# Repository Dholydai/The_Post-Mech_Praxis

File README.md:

# The_Post-Mech_Praxis
The "post-mechanical typewriter mechanical switch keyboard"... for writers born in the third decade of the 21st century.

_This keyboard is hardwired... plug-n-play. It works with the US-English drivers of Windows and Linux._  

The cases were created using https://github.com/jeffminton/keyboard_stl_generator and OpenSCAD. 
The PCB design and controller program were created by Troy Fletcher: https://github.com/TroyFletcher/vim-colors-synthwave

//Released the Rev 2 keyboard case files. The added screwed fasteners make it very solid. I call it "The Slab."

Please visit https://post-mech.com

1. DO NOT BUILD Rev 2: I am tweaking the two-handed design. I must remake the PCB in total with KiCad to create an editable file. Adding a 92nd switch will make finding a keycap set 50 times easier.

2. GET THE PCB WRAPPED IN A CASE BEFORE FIRING IT UP: Static discharge has damaged several controllers on my bare boards. On very rare occasion #1 exhibits flakey output that is by solved by hot-plugging. Suspect static damage.

3. DO NOT MAKE THIS MISTAKE: I did not trim the leads of switch K8 flush with the PCB. The long lead shorted the switch to ground through the USB-C connector. The brand new Elite-C controller was killed on first power-up.

4. TO REPLACE THE CONTROLLER: Desolder the Elite-C as best you can (you must buy an electric desoldering sucker). Carefully break up the little PCB with needle nose pliers, being careful to avoid twisting the headers. Desolder and remove the torn pieces of through-hole barrels stuck to the header pins. Solder the new controller to the old headers.

Note: Received new Rev 2 PCBs from PCBWay for two-hand keyboards, the quality of the PCBs is excellent... built #4. Also built and tested the reversable PCBs for single-hand Dvorak keyboards designed by Troy Fletcher. Both work!

Dholydai

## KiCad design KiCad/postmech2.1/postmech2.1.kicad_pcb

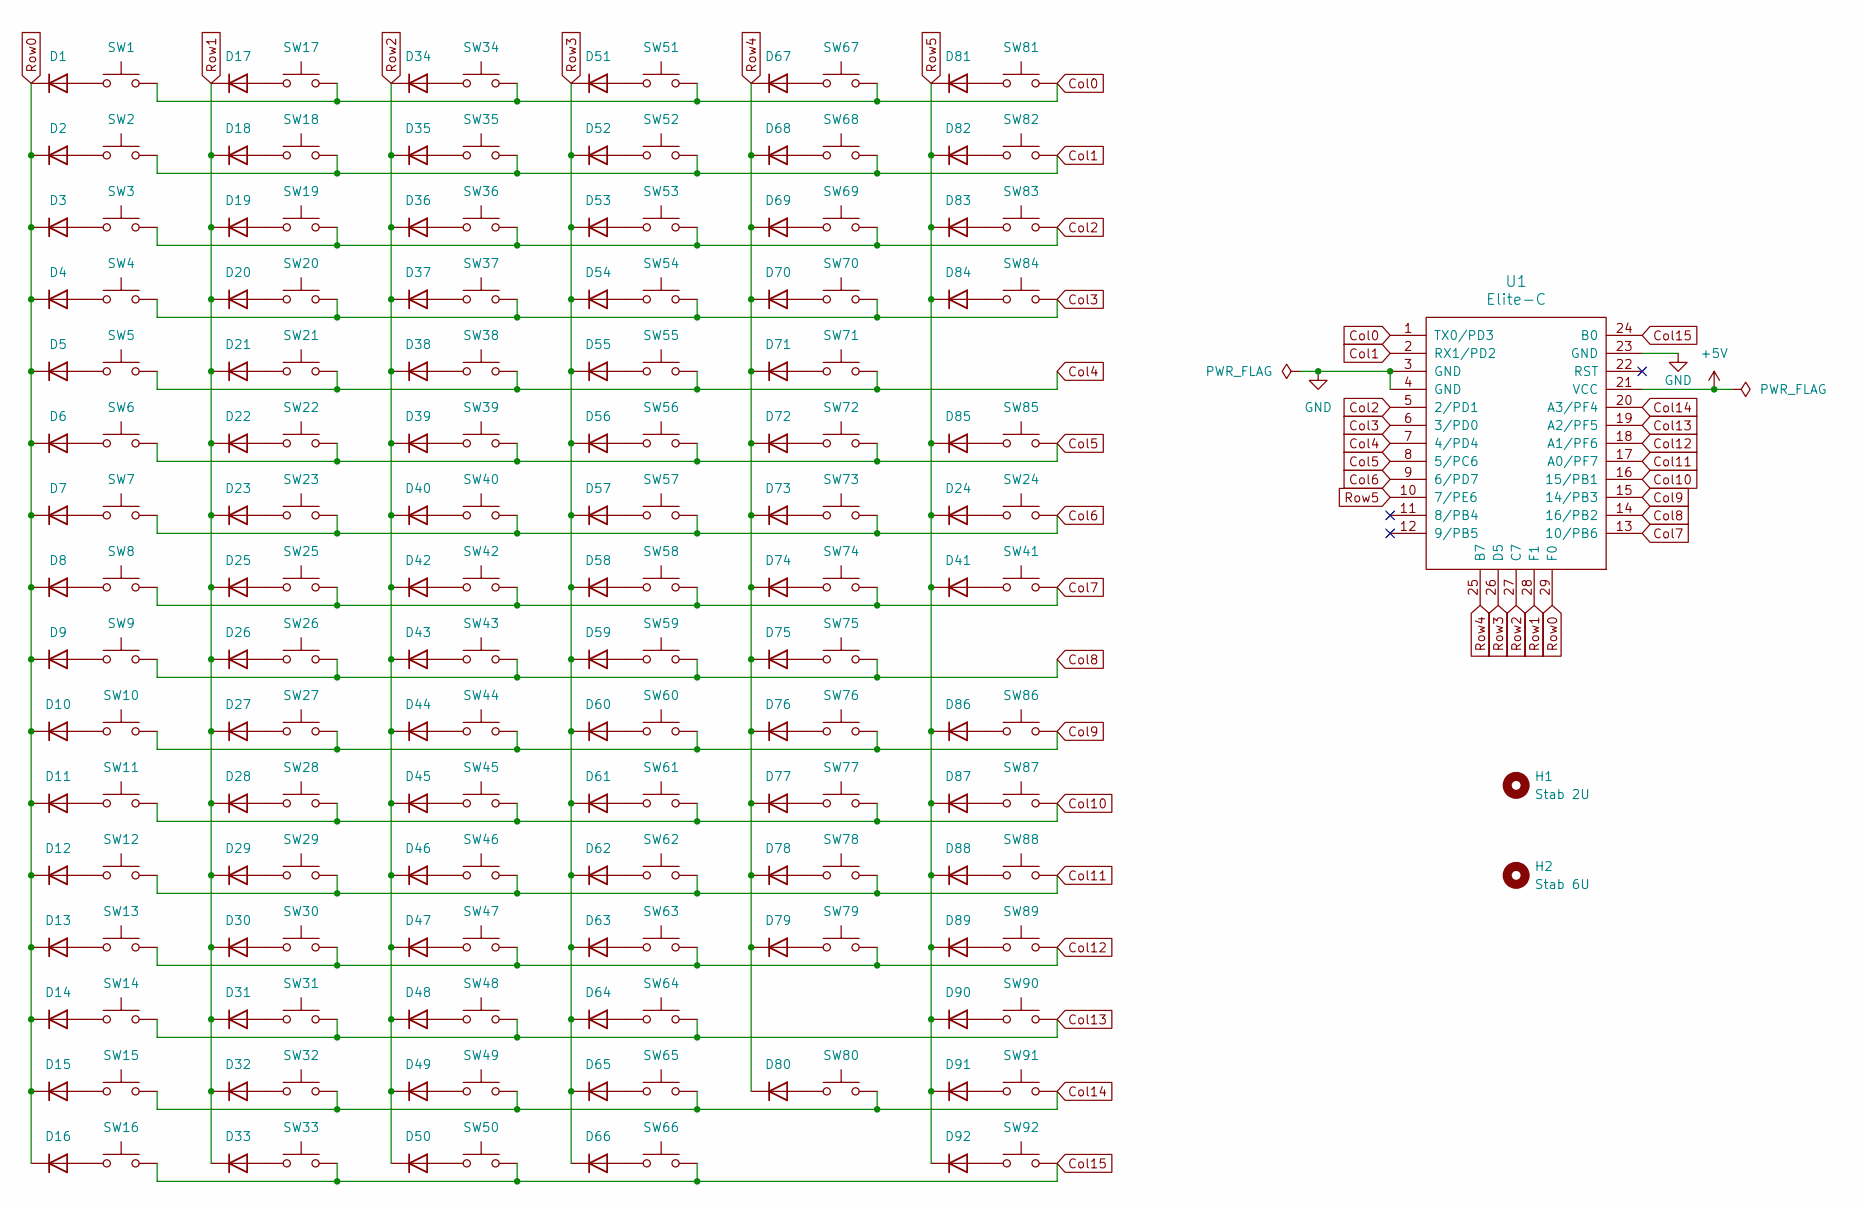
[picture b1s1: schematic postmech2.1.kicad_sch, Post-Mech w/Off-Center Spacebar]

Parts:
D1, D2, D3, D4, D5, D6, D7, D8, D9, D10, D11, D12, D13, D14, D15, D16, D17, D18, D19, D20, D21, D22, D23, D24, D25, D26, D27, D28, D29, D30, D31, D32, D33, D34, D35, D36, D37, D38, D39, D40, D41, D42, D43, D44, D45, D46, D47, D48, D49, D50, D51, D52, D53, D54, D55, D56, D57, D58, D59, D60, D61, D62, D63, D64, D65, D66, D67, D68, D69, D70, D71, D72, D73, D74, D75, D76, D77, D78, D79, D80, D81, D82, D83, D84, D85, D86, D87, D88, D89, D90, D91, D92: 1N4148; Diode_DO-35
H1: Stab 2U; Stabilizer_MX_2.00u
H2: Stab 6U; Stabilizer_MX_6.00u
SW1, SW2, SW3, SW4, SW5, SW6, SW7, SW8, SW9, SW10, SW11, SW12, SW13, SW14, SW15, SW16, SW18, SW19, SW20, SW21, SW22, SW23, SW24, SW25, SW26, SW27, SW28, SW29, SW31, SW32, SW33, SW34, SW35, SW36, SW37, SW38, SW39, SW40, SW41, SW42, SW43, SW44, SW45, SW46, SW47, SW48, SW49, SW50, SW52, SW53, SW54, SW55, SW56, SW58, SW59, SW60, SW61, SW62, SW64, SW65, SW66, SW68, SW69, SW70, SW71, SW72, SW74, SW75, SW76, SW77, SW78, SW80, SW82, SW83, SW87, SW88, SW90, SW91, SW92: SW_Push; MX_PCB_1.00u
SW17, SW30, SW67, SW79: SW_Push; MX_PCB_1.50u
SW51, SW63: SW_Push; MX_PCB_1.75u
SW57, SW81, SW84, SW86, SW89: SW_Push; MX_PCB_1.25u
SW73: SW_Push; MX_PCB_2.00u
SW85: SW_Push; MX_PCB_6.00u_Offset
U1: Elite-C

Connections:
+5V: U1.21 (VCC)
Col0: SW1.2, SW17.2, SW34.2, SW51.2, SW67.2, SW81.2, U1.1 (TX0/PD3)
Col1: SW2.2, SW18.2, SW35.2, SW52.2, SW68.2, SW82.2, U1.2 (RX1/PD2)
Col2: SW3.2, SW19.2, SW36.2, SW53.2, SW69.2, SW83.2, U1.5 (2/PD1)
Col3: SW4.2, SW20.2, SW37.2, SW54.2, SW70.2, SW84.2, U1.6 (3/PD0)
Col4: SW5.2, SW21.2, SW38.2, SW55.2, SW71.2, U1.7 (4/PD4)
Col5: SW6.2, SW22.2, SW39.2, SW56.2, SW72.2, SW85.2, U1.8 (5/PC6)
Col6: SW7.2, SW23.2, SW24.2, SW40.2, SW57.2, SW73.2, U1.9 (6/PD7)
Col7: SW8.2, SW25.2, SW41.2, SW42.2, SW58.2, SW74.2, U1.13 (10/PB6)
Col8: SW9.2, SW26.2, SW43.2, SW59.2, SW75.2, U1.14 (16/PB2)
Col9: SW10.2, SW27.2, SW44.2, SW60.2, SW76.2, SW86.2, U1.15 (14/PB3)
Col10: SW11.2, SW28.2, SW45.2, SW61.2, SW77.2, SW87.2, U1.16 (15/PB1)
Col11: SW12.2, SW29.2, SW46.2, SW62.2, SW78.2, SW88.2, U1.17 (A0/PF7)
Col12: SW13.2, SW30.2, SW47.2, SW63.2, SW79.2, SW89.2, U1.18 (A1/PF6)
Col13: SW14.2, SW31.2, SW48.2, SW64.2, SW90.2, U1.19 (A2/PF5)
Col14: SW15.2, SW32.2, SW49.2, SW65.2, SW80.2, SW91.2, U1.20 (A3/PF4)
Col15: SW16.2, SW33.2, SW50.2, SW66.2, SW92.2, U1.24 (B0)
GND: U1.3 (GND), U1.4 (GND), U1.23 (GND)
unnamed: D1.2 (A), SW1.1
unnamed: D2.2 (A), SW2.1
unnamed: D3.2 (A), SW3.1
unnamed: D4.2 (A), SW4.1
unnamed: D5.2 (A), SW5.1
unnamed: D6.2 (A), SW6.1
unnamed: D7.2 (A), SW7.1
unnamed: D8.2 (A), SW8.1
unnamed: D9.2 (A), SW9.1
unnamed: D10.2 (A), SW10.1
unnamed: D11.2 (A), SW11.1
unnamed: D12.2 (A), SW12.1
unnamed: D13.2 (A), SW13.1
unnamed: D14.2 (A), SW14.1
unnamed: D15.2 (A), SW15.1
unnamed: D16.2 (A), SW16.1
unnamed: D17.2 (A), SW17.1
unnamed: D18.2 (A), SW18.1
unnamed: D19.2 (A), SW19.1
unnamed: D20.2 (A), SW20.1
unnamed: D21.2 (A), SW21.1
unnamed: D22.2 (A), SW22.1
unnamed: D23.2 (A), SW23.1
unnamed: D24.2 (A), SW24.1
unnamed: D25.2 (A), SW25.1
unnamed: D26.2 (A), SW26.1
unnamed: D27.2 (A), SW27.1
unnamed: D28.2 (A), SW28.1
unnamed: D29.2 (A), SW29.1
unnamed: D30.2 (A), SW30.1
unnamed: D31.2 (A), SW31.1
unnamed: D32.2 (A), SW32.1
unnamed: D33.2 (A), SW33.1
unnamed: D34.2 (A), SW34.1
unnamed: D35.2 (A), SW35.1
unnamed: D36.2 (A), SW36.1
unnamed: D37.2 (A), SW37.1
unnamed: D38.2 (A), SW38.1
unnamed: D39.2 (A), SW39.1
unnamed: D40.2 (A), SW40.1
unnamed: D41.2 (A), SW41.1
unnamed: D42.2 (A), SW42.1
unnamed: D43.2 (A), SW43.1
unnamed: D44.2 (A), SW44.1
unnamed: D45.2 (A), SW45.1
unnamed: D46.2 (A), SW46.1
unnamed: D47.2 (A), SW47.1
unnamed: D48.2 (A), SW48.1
unnamed: D49.2 (A), SW49.1
unnamed: D50.2 (A), SW50.1
unnamed: D51.2 (A), SW51.1
unnamed: D52.2 (A), SW52.1
unnamed: D53.2 (A), SW53.1
unnamed: D54.2 (A), SW54.1
unnamed: D55.2 (A), SW55.1
unnamed: D56.2 (A), SW56.1
unnamed: D57.2 (A), SW57.1
unnamed: D58.2 (A), SW58.1
unnamed: D59.2 (A), SW59.1
unnamed: D60.2 (A), SW60.1
unnamed: D61.2 (A), SW61.1
unnamed: D62.2 (A), SW62.1
unnamed: D63.2 (A), SW63.1
unnamed: D64.2 (A), SW64.1
unnamed: D65.2 (A), SW65.1
unnamed: D66.2 (A), SW66.1
unnamed: D67.2 (A), SW67.1
unnamed: D68.2 (A), SW68.1
unnamed: D69.2 (A), SW69.1
unnamed: D70.2 (A), SW70.1
unnamed: D71.2 (A), SW71.1
unnamed: D72.2 (A), SW72.1
unnamed: D73.2 (A), SW73.1
unnamed: D74.2 (A), SW74.1
unnamed: D75.2 (A), SW75.1
unnamed: D76.2 (A), SW76.1
unnamed: D77.2 (A), SW77.1
unnamed: D78.2 (A), SW78.1
unnamed: D79.2 (A), SW79.1
unnamed: D80.2 (A), SW80.1
unnamed: D81.2 (A), SW81.1
unnamed: D82.2 (A), SW82.1
unnamed: D83.2 (A), SW83.1
unnamed: D84.2 (A), SW84.1
unnamed: D85.2 (A), SW85.1
unnamed: D86.2 (A), SW86.1
unnamed: D87.2 (A), SW87.1
unnamed: D88.2 (A), SW88.1
unnamed: D89.2 (A), SW89.1
unnamed: D90.2 (A), SW90.1
unnamed: D91.2 (A), SW91.1
unnamed: D92.2 (A), SW92.1
Row0: D1.1 (K), D2.1 (K), D3.1 (K), D4.1 (K), D5.1 (K), D6.1 (K), D7.1 (K), D8.1 (K), D9.1 (K), D10.1 (K), D11.1 (K), D12.1 (K), D13.1 (K), D14.1 (K), D15.1 (K), D16.1 (K), U1.29 (F0)
Row1: D17.1 (K), D18.1 (K), D19.1 (K), D20.1 (K), D21.1 (K), D22.1 (K), D23.1 (K), D25.1 (K), D26.1 (K), D27.1 (K), D28.1 (K), D29.1 (K), D30.1 (K), D31.1 (K), D32.1 (K), D33.1 (K), U1.28 (F1)
Row2: D34.1 (K), D35.1 (K), D36.1 (K), D37.1 (K), D38.1 (K), D39.1 (K), D40.1 (K), D42.1 (K), D43.1 (K), D44.1 (K), D45.1 (K), D46.1 (K), D47.1 (K), D48.1 (K), D49.1 (K), D50.1 (K), U1.27 (C7)
Row3: D51.1 (K), D52.1 (K), D53.1 (K), D54.1 (K), D55.1 (K), D56.1 (K), D57.1 (K), D58.1 (K), D59.1 (K), D60.1 (K), D61.1 (K), D62.1 (K), D63.1 (K), D64.1 (K), D65.1 (K), D66.1 (K), U1.26 (D5)
Row4: D67.1 (K), D68.1 (K), D69.1 (K), D70.1 (K), D71.1 (K), D72.1 (K), D73.1 (K), D74.1 (K), D75.1 (K), D76.1 (K), D77.1 (K), D78.1 (K), D79.1 (K), D80.1 (K), U1.25 (B7)
Row5: D24.1 (K), D41.1 (K), D81.1 (K), D82.1 (K), D83.1 (K), D84.1 (K), D85.1 (K), D86.1 (K), D87.1 (K), D88.1 (K), D89.1 (K), D90.1 (K), D91.1 (K), D92.1 (K), U1.10 (7/PE6)

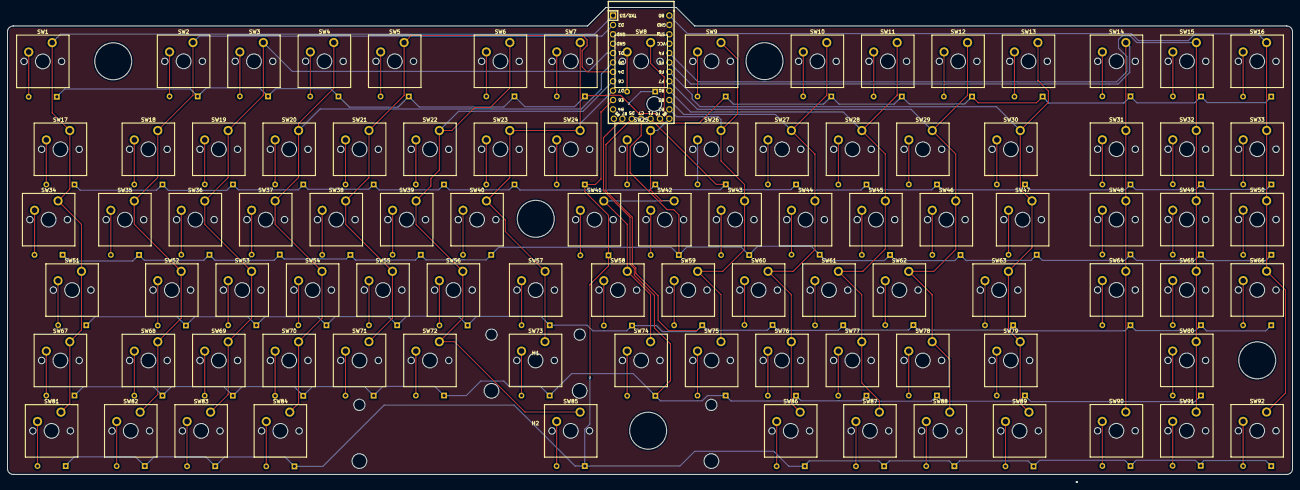
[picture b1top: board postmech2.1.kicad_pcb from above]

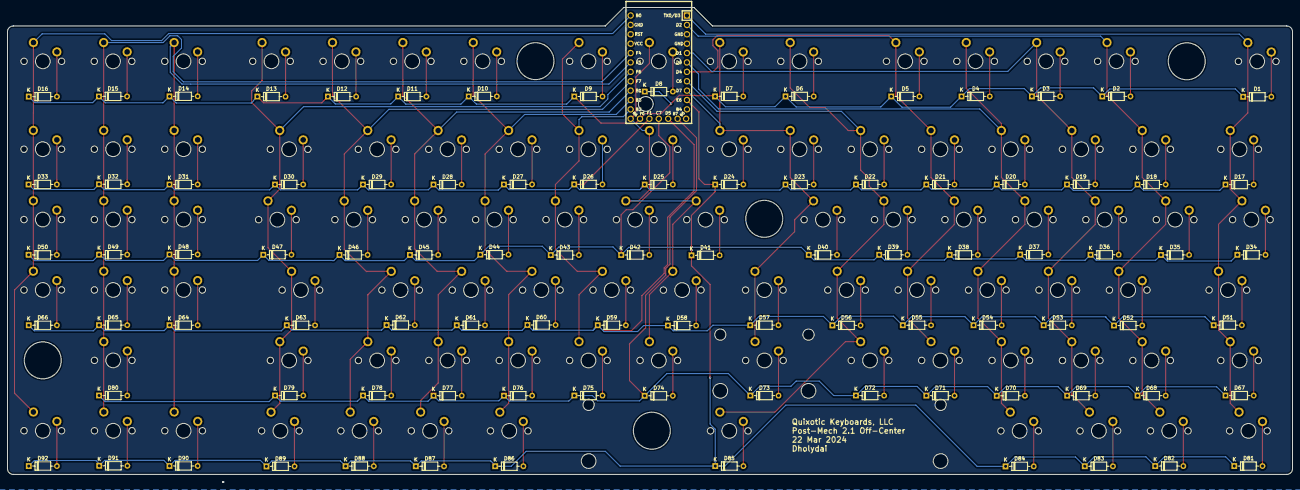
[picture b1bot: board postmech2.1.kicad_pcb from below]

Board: 2 copper layers, 347.8 x 128.5 mm, 187 parts (92 on the bottom side), 115 nets.

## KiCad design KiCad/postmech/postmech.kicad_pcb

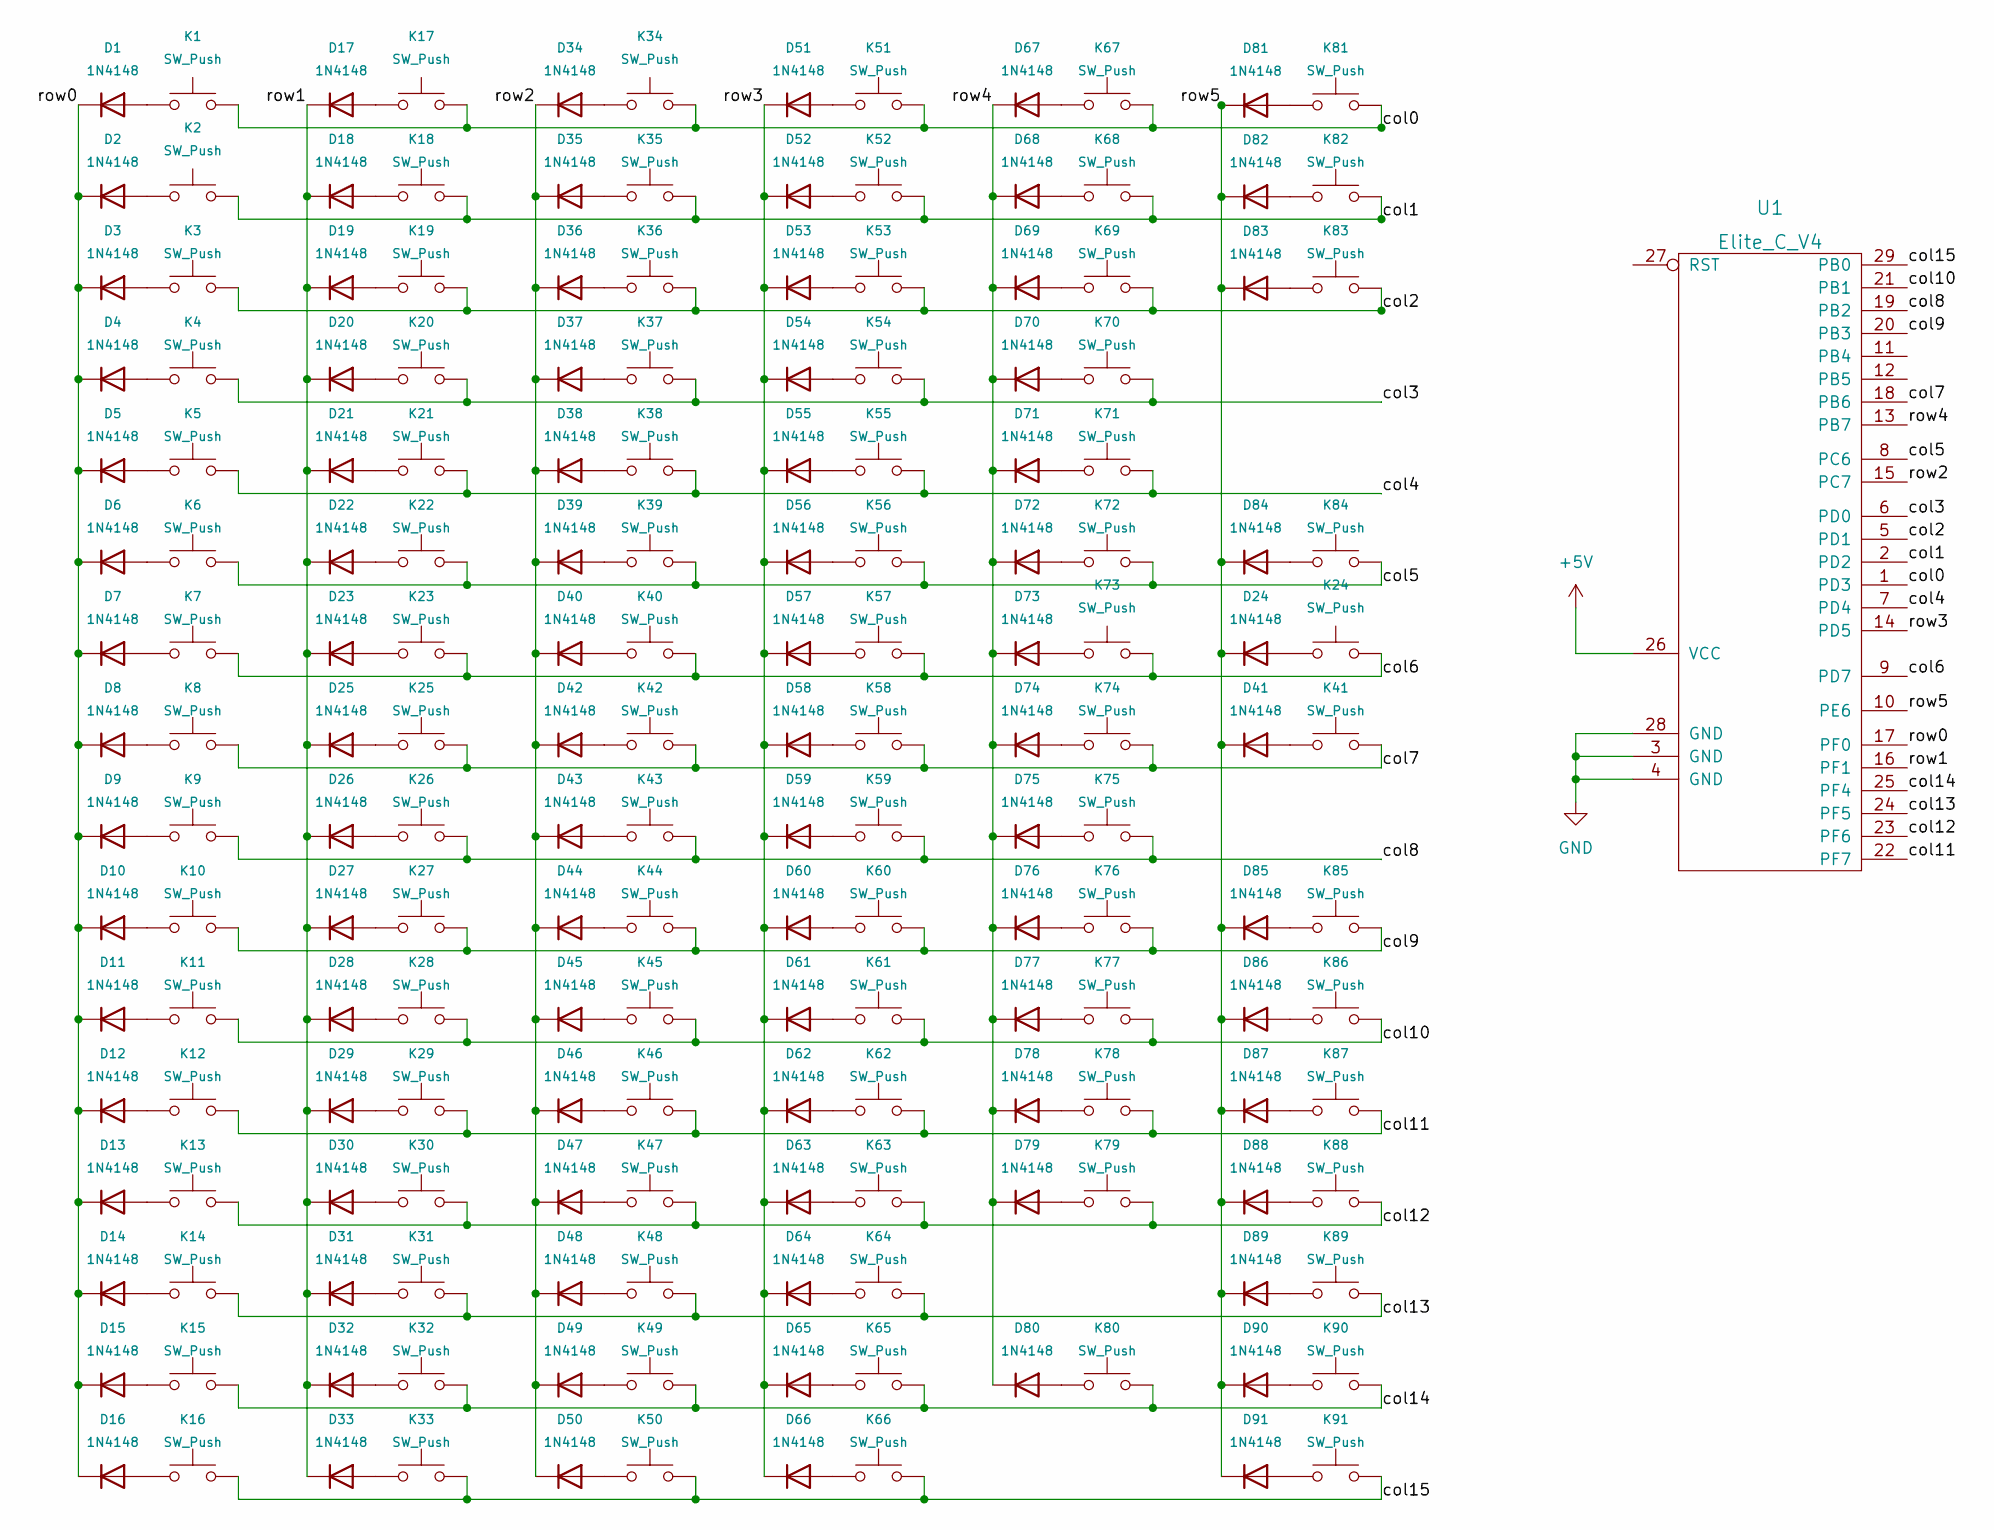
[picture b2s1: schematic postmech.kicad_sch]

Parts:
D1, D2, D3, D4, D5, D6, D7, D8, D9, D10, D11, D12, D13, D14, D15, D16, D17, D18, D19, D20, D21, D22, D23, D24, D25, D26, D27, D28, D29, D30, D31, D32, D33, D34, D35, D36, D37, D38, D39, D40, D41, D42, D43, D44, D45, D46, D47, D48, D49, D50, D51, D52, D53, D54, D55, D56, D57, D58, D59, D60, D61, D62, D63, D64, D65, D66, D67, D68, D69, D70, D71, D72, D73, D74, D75, D76, D77, D78, D79, D80, D81, D82, D83, D84, D85, D86, D87, D88, D89, D90, D91: 1N4148; D_SOD123_noSM_v1.0
K1, K2, K3, K4, K5, K6, K7, K8, K9, K10, K11, K12, K13, K14, K15, K16, K17, K18, K19, K20, K21, K22, K23, K24, K25, K26, K27, K28, K29, K30, K31, K32, K33, K34, K35, K36, K37, K38, K39, K40, K41, K42, K43, K44, K45, K46, K47, K48, K49, K50, K51, K52, K53, K54, K55, K56, K57, K58, K59, K60, K61, K62, K63, K64, K65, K66, K67, K68, K69, K70, K71, K72, K73, K74, K75, K76, K77, K78, K79, K80, K81, K82, K83, K84, K85, K86, K87, K88, K89, K90, K91: SW_Push; Mx_ONLY_100
U1: Elite_C_V4; Teensy2.0_text_mod_v1.2

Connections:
+5V: U1.26 (VCC)
/col0: K1.2, K17.2, K34.2, K51.2, K67.2, K81.2, U1.1 (PD3)
/col1: K2.2, K18.2, K35.2, K52.2, K68.2, K82.2, U1.2 (PD2)
/col2: K3.2, K19.2, K36.2, K53.2, K69.2, K83.2, U1.5 (PD1)
/col3: K4.2, K20.2, K37.2, K54.2, K70.2, U1.6 (PD0)
/col4: K5.2, K21.2, K38.2, K55.2, K71.2, U1.7 (PD4)
/col5: K6.2, K22.2, K39.2, K56.2, K72.2, K84.2, U1.8 (PC6)
/col6: K7.2, K23.2, K24.2, K40.2, K57.2, K73.2, U1.9 (PD7)
/col7: K8.2, K25.2, K41.2, K42.2, K58.2, K74.2, U1.18 (PB6)
/col8: K9.2, K26.2, K43.2, K59.2, K75.2, U1.19 (PB2)
/col9: K10.2, K27.2, K44.2, K60.2, K76.2, K85.2, U1.20 (PB3)
/col10: K11.2, K28.2, K45.2, K61.2, K77.2, K86.2, U1.21 (PB1)
/col11: K12.2, K29.2, K46.2, K62.2, K78.2, K87.2, U1.22 (PF7)
/col12: K13.2, K30.2, K47.2, K63.2, K79.2, K88.2, U1.23 (PF6)
/col13: K14.2, K31.2, K48.2, K64.2, K89.2, U1.24 (PF5)
/col14: K15.2, K32.2, K49.2, K65.2, K80.2, K90.2, U1.25 (PF4)
/col15: K16.2, K33.2, K50.2, K66.2, K91.2, U1.29 (PB0)
/row0: D1.1 (K), D2.1 (K), D3.1 (K), D4.1 (K), D5.1 (K), D6.1 (K), D7.1 (K), D8.1 (K), D9.1 (K), D10.1 (K), D11.1 (K), D12.1 (K), D13.1 (K), D14.1 (K), D15.1 (K), D16.1 (K), U1.17 (PF0)
/row1: D17.1 (K), D18.1 (K), D19.1 (K), D20.1 (K), D21.1 (K), D22.1 (K), D23.1 (K), D25.1 (K), D26.1 (K), D27.1 (K), D28.1 (K), D29.1 (K), D30.1 (K), D31.1 (K), D32.1 (K), D33.1 (K), U1.16 (PF1)
/row2: D34.1 (K), D35.1 (K), D36.1 (K), D37.1 (K), D38.1 (K), D39.1 (K), D40.1 (K), D42.1 (K), D43.1 (K), D44.1 (K), D45.1 (K), D46.1 (K), D47.1 (K), D48.1 (K), D49.1 (K), D50.1 (K), U1.15 (PC7)
/row3: D51.1 (K), D52.1 (K), D53.1 (K), D54.1 (K), D55.1 (K), D56.1 (K), D57.1 (K), D58.1 (K), D59.1 (K), D60.1 (K), D61.1 (K), D62.1 (K), D63.1 (K), D64.1 (K), D65.1 (K), D66.1 (K), U1.14 (PD5)
/row4: D67.1 (K), D68.1 (K), D69.1 (K), D70.1 (K), D71.1 (K), D72.1 (K), D73.1 (K), D74.1 (K), D75.1 (K), D76.1 (K), D77.1 (K), D78.1 (K), D79.1 (K), D80.1 (K), U1.13 (PB7)
/row5: D24.1 (K), D41.1 (K), D81.1 (K), D82.1 (K), D83.1 (K), D84.1 (K), D85.1 (K), D86.1 (K), D87.1 (K), D88.1 (K), D89.1 (K), D90.1 (K), D91.1 (K), U1.10 (PE6)
GND: U1.3 (GND), U1.4 (GND), U1.28 (GND)
unnamed: D1.2 (A), K1.1
unnamed: D2.2 (A), K2.1
unnamed: D3.2 (A), K3.1
unnamed: D4.2 (A), K4.1
unnamed: D5.2 (A), K5.1
unnamed: D6.2 (A), K6.1
unnamed: D7.2 (A), K7.1
unnamed: D8.2 (A), K8.1
unnamed: D9.2 (A), K9.1
unnamed: D10.2 (A), K10.1
unnamed: D11.2 (A), K11.1
unnamed: D12.2 (A), K12.1
unnamed: D13.2 (A), K13.1
unnamed: D14.2 (A), K14.1
unnamed: D15.2 (A), K15.1
unnamed: D16.2 (A), K16.1
unnamed: D17.2 (A), K17.1
unnamed: D18.2 (A), K18.1
unnamed: D19.2 (A), K19.1
unnamed: D20.2 (A), K20.1
unnamed: D21.2 (A), K21.1
unnamed: D22.2 (A), K22.1
unnamed: D23.2 (A), K23.1
unnamed: D24.2 (A), K24.1
unnamed: D25.2 (A), K25.1
unnamed: D26.2 (A), K26.1
unnamed: D27.2 (A), K27.1
unnamed: D28.2 (A), K28.1
unnamed: D29.2 (A), K29.1
unnamed: D30.2 (A), K30.1
unnamed: D31.2 (A), K31.1
unnamed: D32.2 (A), K32.1
unnamed: D33.2 (A), K33.1
unnamed: D34.2 (A), K34.1
unnamed: D35.2 (A), K35.1
unnamed: D36.2 (A), K36.1
unnamed: D37.2 (A), K37.1
unnamed: D38.2 (A), K38.1
unnamed: D39.2 (A), K39.1
unnamed: D40.2 (A), K40.1
unnamed: D41.2 (A), K41.1
unnamed: D42.2 (A), K42.1
unnamed: D43.2 (A), K43.1
unnamed: D44.2 (A), K44.1
unnamed: D45.2 (A), K45.1
unnamed: D46.2 (A), K46.1
unnamed: D47.2 (A), K47.1
unnamed: D48.2 (A), K48.1
unnamed: D49.2 (A), K49.1
unnamed: D50.2 (A), K50.1
unnamed: D51.2 (A), K51.1
unnamed: D52.2 (A), K52.1
unnamed: D53.2 (A), K53.1
unnamed: D54.2 (A), K54.1
unnamed: D55.2 (A), K55.1
unnamed: D56.2 (A), K56.1
unnamed: D57.2 (A), K57.1
unnamed: D58.2 (A), K58.1
unnamed: D59.2 (A), K59.1
unnamed: D60.2 (A), K60.1
unnamed: D61.2 (A), K61.1
unnamed: D62.2 (A), K62.1
unnamed: D63.2 (A), K63.1
unnamed: D64.2 (A), K64.1
unnamed: D65.2 (A), K65.1
unnamed: D66.2 (A), K66.1
unnamed: D67.2 (A), K67.1
unnamed: D68.2 (A), K68.1
unnamed: D69.2 (A), K69.1
unnamed: D70.2 (A), K70.1
unnamed: D71.2 (A), K71.1
unnamed: D72.2 (A), K72.1
unnamed: D73.2 (A), K73.1
unnamed: D74.2 (A), K74.1
unnamed: D75.2 (A), K75.1
unnamed: D76.2 (A), K76.1
unnamed: D77.2 (A), K77.1
unnamed: D78.2 (A), K78.1
unnamed: D79.2 (A), K79.1
unnamed: D80.2 (A), K80.1
unnamed: D81.2 (A), K81.1
unnamed: D82.2 (A), K82.1
unnamed: D83.2 (A), K83.1
unnamed: D84.2 (A), K84.1
unnamed: D85.2 (A), K85.1
unnamed: D86.2 (A), K86.1
unnamed: D87.2 (A), K87.1
unnamed: D88.2 (A), K88.1
unnamed: D89.2 (A), K89.1
unnamed: D90.2 (A), K90.1
unnamed: D91.2 (A), K91.1

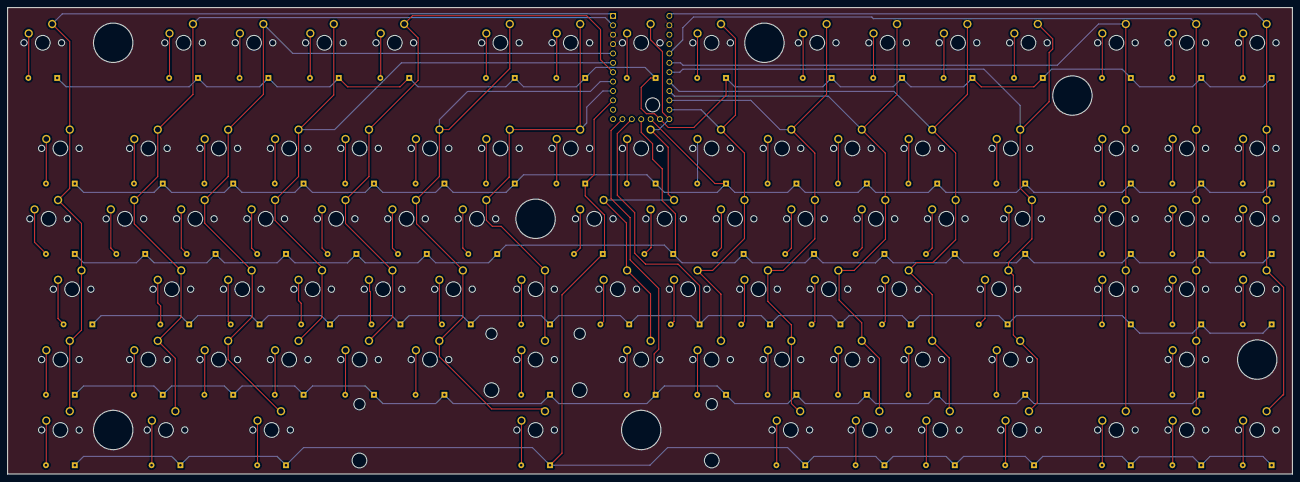
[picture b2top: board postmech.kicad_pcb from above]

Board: 2 copper layers, 347.7 x 126.2 mm, 183 parts (0 on the bottom side), 114 nets.

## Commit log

2023-12-29 Add files via upload
    Files for use with Jeffminton/keyboard_stl_generator
2023-12-31 Corrected the offset tower trough hole
2023-12-31 Rename CaseBtmRgt-1.0.stl to CaseBtmRgt.stl
2024-01-03 Photo gallery
2024-01-03 Files to create keyboard cases
2024-01-03 Files to create PCBs including a Reversable single-hand keyboard PCB
2024-01-03 Files to program the controller
2024-01-03 Files create 3D models of keyboard cases
2024-01-03 3D model files for printing keyboard cases
2024-01-03 Finally!
2024-01-03 Ego sum Post-Mech, non ducor, duco.
2024-01-05 Corrected x-axis dimensions
2024-01-08 Abandoned patent application
    The last version of the patent application, archived before pruning out the Dvorak modification for languages beyond English. The "clean" version was submitted to my Patent Attorney. The final patent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
2024-01-08 Dvorak for languages beyond English
2024-01-08 Files for QMK and Keyboard Firmware Builder
2024-01-08 File for QMK firmware burning
2024-01-08 Files for QMK firmware burner
2024-01-08 File for Keyboard Firmware Builder
2024-01-19 Advice for builders
2024-01-20 Updated case design by adding mechanical connections
2024-01-20 Update case design by adding mechanical connections
2024-01-23 Corrected aft connector location
2024-03-24 Add files via upload
    Two-Hand Post-Mech w/off-center spacebar switch
